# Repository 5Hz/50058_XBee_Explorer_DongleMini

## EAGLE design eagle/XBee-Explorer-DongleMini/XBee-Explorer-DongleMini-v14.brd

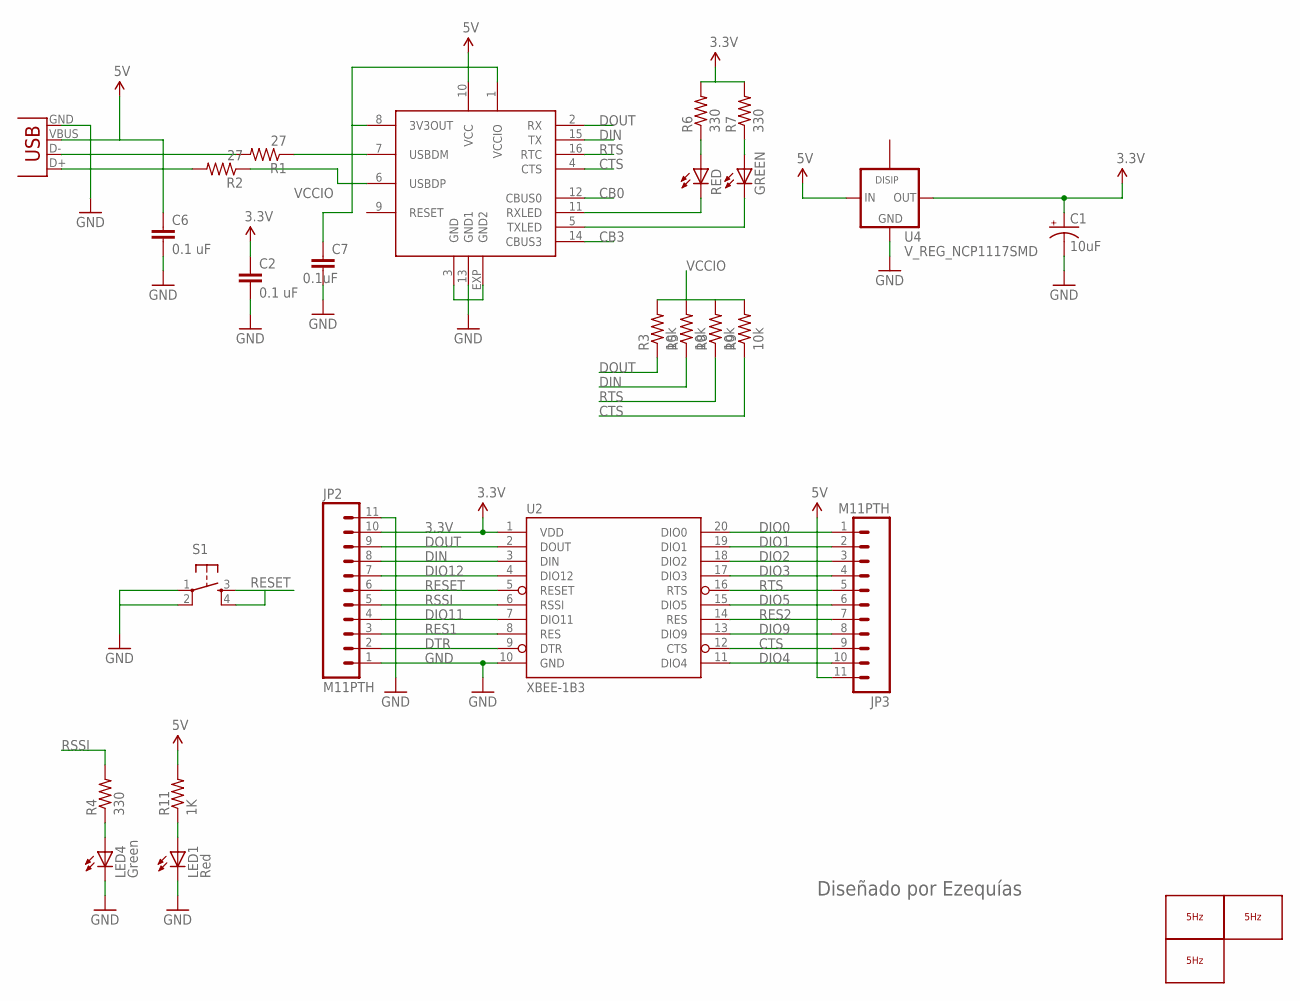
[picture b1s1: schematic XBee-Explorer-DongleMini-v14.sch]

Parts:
C1: 10uF; EIA3216
C2, C6: 0.1 uF; 0603-CAP
C7: 0.1uF; 0603-CAP
GREEN: LED0603; LED-0603
JP2, JP3: M11PTH; 1X11
LED1: Red; LED-0603
LED4: Green; LED-0603
LOGO2: LOGO_5HZ_H_10MM; 5HZ_LOGO_H_10MM
LOGO3: LOGO_5HZ_H_COOPER_15MM; 5HZ_LOGO_H_COOPER_15MM
LOGO4: LOGO_5HZ_WEB_COOPER_10MM; 5HZ_WEB_COOPER_10MM
R1, R2: 27; 0603-RES
R3, R5, R8, R9: 10k; 0603-RES
R4, R6, R7: 330; 0603-RES
R11: 1K; 0603-RES
RED: LED0603; LED-0603
S1: TAC_SWITCHSMD; TACTILE_SWITCH_SMD
U2: XBEE-1B3; XBEE-SMD
U4: V_REG_NCP1117SMD; SOT223
U$5: FT230; QFN-16
X1: USBSMD; USB-MINIB

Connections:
3.3V: C1.A (+), C2.1, JP2.10, R6.2, R7.2, U2.1 (VDD), U4.2 (OUT)
5V: C6.1, JP3.11, R11.2, U4.3 (IN), U$5.10 (VCC), X1.VBUS
CB0: U$5.12 (CBUS0)
CB3: U$5.14 (CBUS3)
CTS: JP3.9, R9.1, U2.12 (CTS), U$5.4 (CTS)
DIN: JP2.8, R5.1, U2.3 (DIN), U$5.15 (TX)
DIO0: JP3.1, U2.20 (DIO0)
DIO1: JP3.2, U2.19 (DIO1)
DIO2: JP3.3, U2.18 (DIO2)
DIO3: JP3.4, U2.17 (DIO3)
DIO4: JP3.10, U2.11 (DIO4)
DIO5: JP3.6, U2.15 (DIO5)
DIO9: JP3.8, U2.13 (DIO9)
DIO11: JP2.4, U2.7 (DIO11)
DIO12: JP2.7, U2.4 (DIO12)
DOUT: JP2.9, R3.1, U2.2 (DOUT), U$5.2 (RX)
DTR: JP2.2, U2.9 (DTR)
GND: C1.C (-), C2.2, C6.2, C7.2, JP2.1, JP2.11, LED1.C, LED4.C, S1.1, S1.2, U2.10 (GND), U4.1 (GND), U$5.3 (GND), U$5.13 (GND1), U$5.EXP (GND2), X1.GND
unnamed: R2.1, U$5.6 (USBDP)
unnamed: LED4.A, R4.1
unnamed: R1.1, U$5.7 (USBDM)
unnamed: R1.2, X1.D-
unnamed: R2.2, X1.D+
unnamed: GREEN.A, R7.1
unnamed: R6.1, RED.A
unnamed: RED.C, U$5.11 (RXLED)
unnamed: GREEN.C, U$5.5 (TXLED)
unnamed: LED1.A, R11.1
RES1: JP2.3, U2.8 (RES)
RES2: JP3.7, U2.14 (RES)
RESET: JP2.6, S1.3, S1.4, U2.5 (RESET)
RSSI: JP2.5, R4.2, U2.6 (RSSI)
RTS: JP3.5, R8.1, U2.16 (RTS), U$5.16 (RTC)
VCCIO: C7.1, R3.2, R5.2, R8.2, R9.2, U$5.1 (VCCIO), U$5.8 (3V3OUT)

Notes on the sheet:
Diseñado por Ezequías

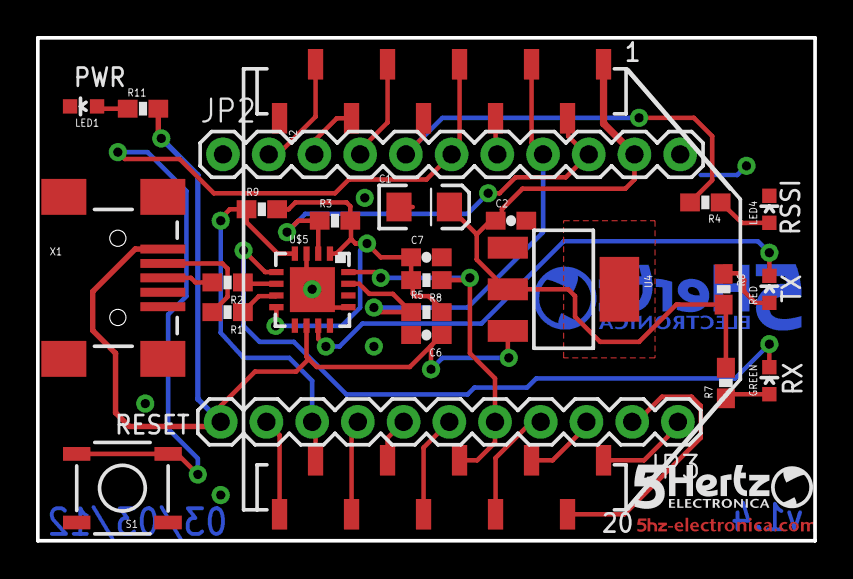
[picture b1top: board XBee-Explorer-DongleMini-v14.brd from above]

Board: 2 copper layers, 43.2 x 27.9 mm, 28 parts (1 on the bottom side), 32 nets.

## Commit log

2014-01-13 creación
